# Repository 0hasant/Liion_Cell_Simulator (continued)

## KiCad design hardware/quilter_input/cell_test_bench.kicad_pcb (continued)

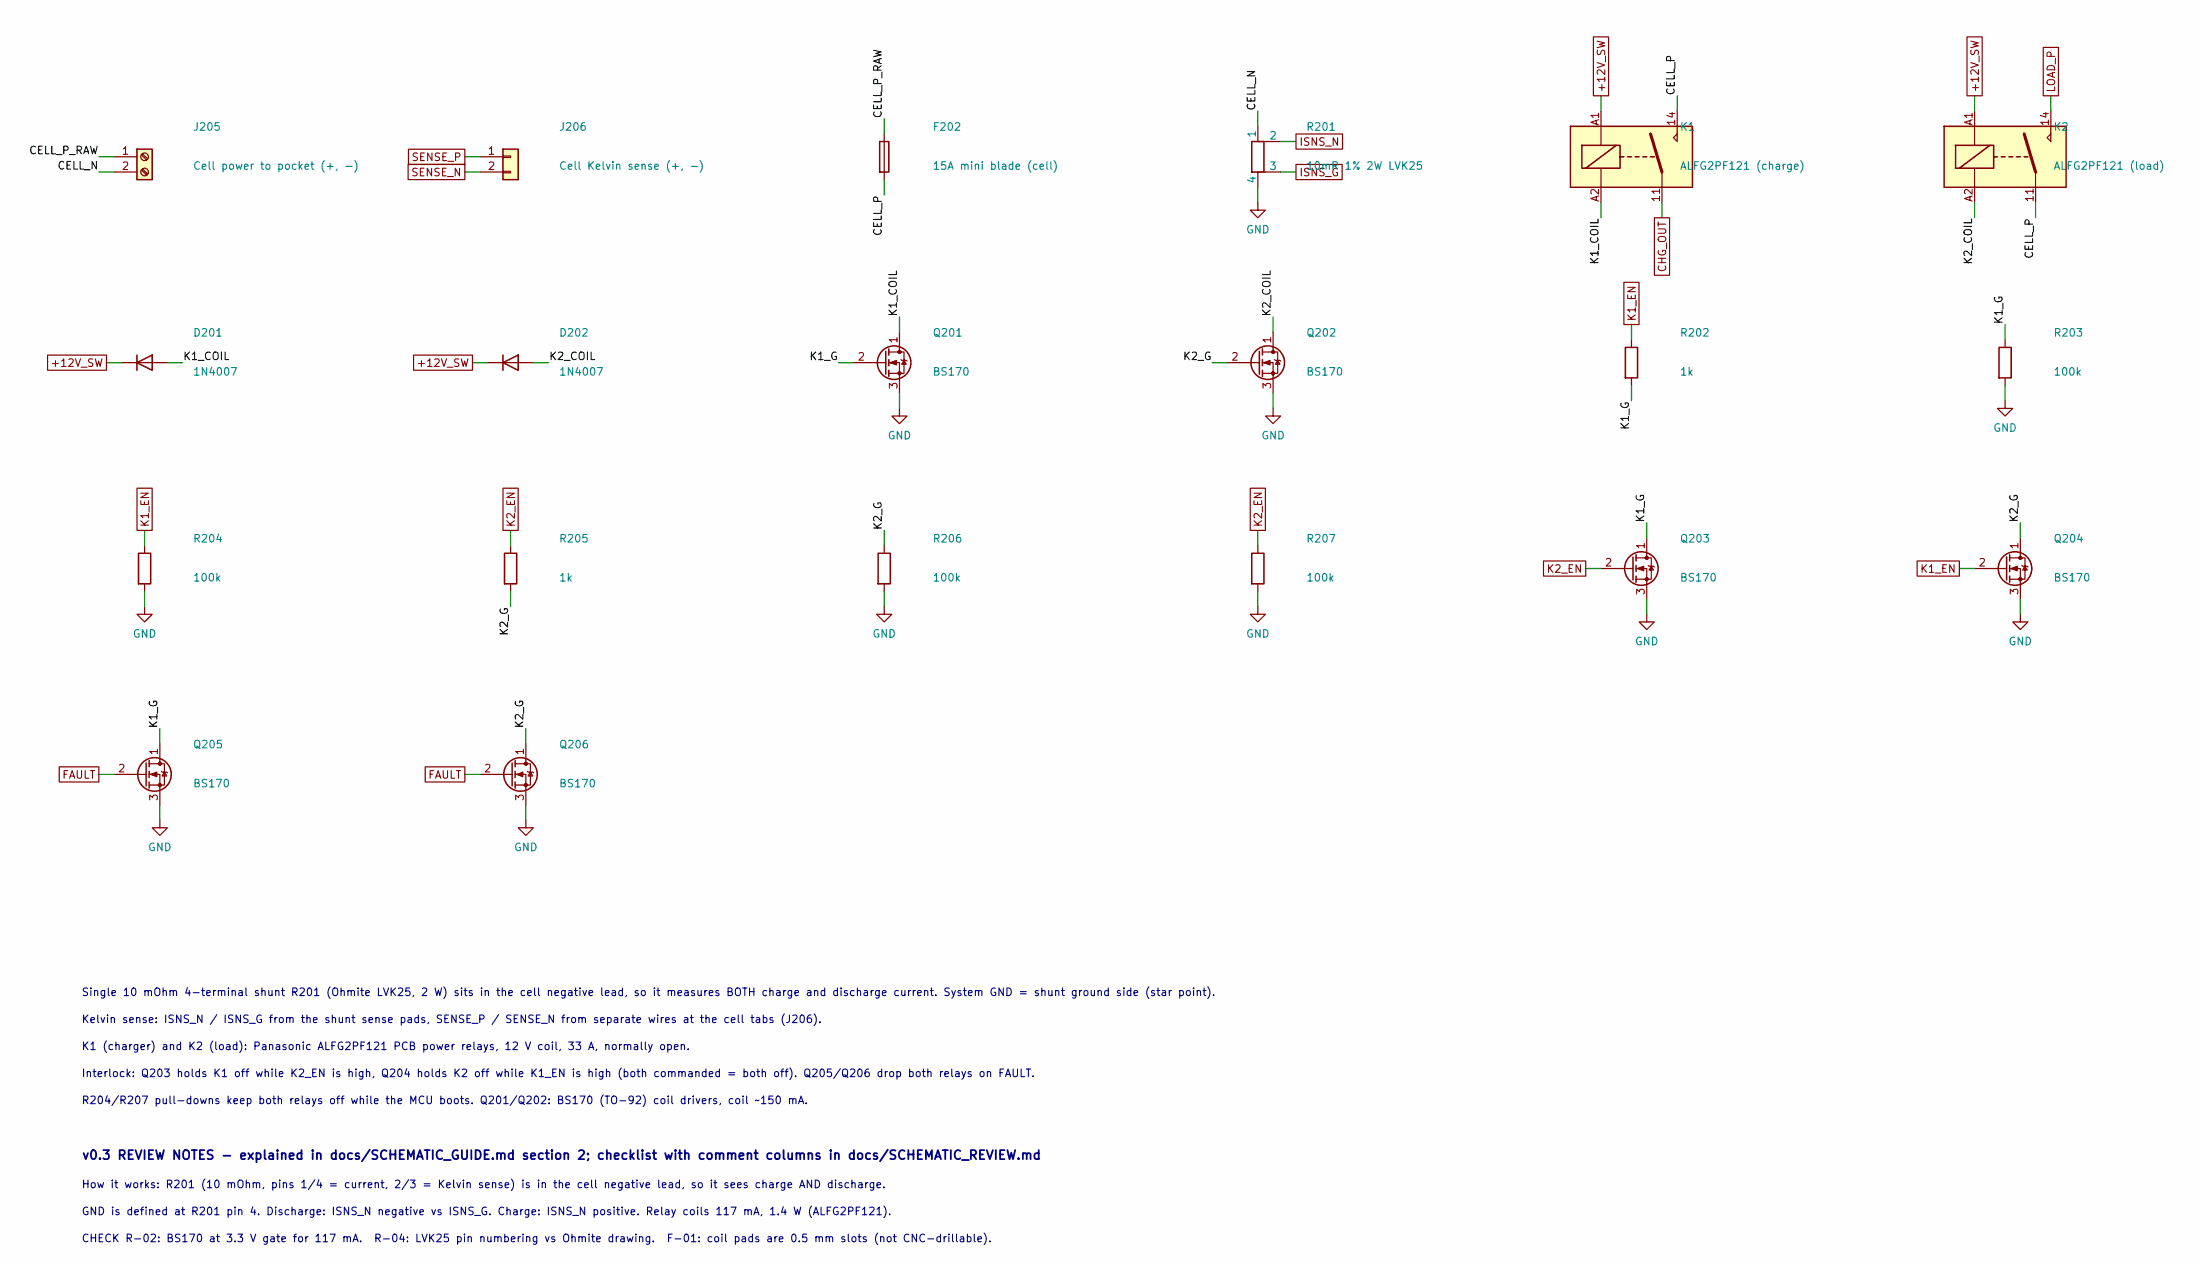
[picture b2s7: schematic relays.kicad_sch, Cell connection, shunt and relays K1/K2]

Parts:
D201, D202: 1N4007; D_DO-41_SOD81_P10.16mm_Horizontal; MPN 1N4007-E3/54
F202: 15A mini blade (cell); Fuseholder_Blade_Mini_Keystone_3568; MPN Keystone 3568
J205: Cell power to pocket (+, -); TerminalBlock_Phoenix_MKDS-3-2-5.08_1x02_P5.08mm_Horizontal
J206: Cell Kelvin sense (+, -); JST_XH_B2B-XH-A_1x02_P2.50mm_Vertical
K1: ALFG2PF121 (charge); Relay_SPST_Panasonic_ALFG_FormA; MPN ALFG2PF121
K2: ALFG2PF121 (load); Relay_SPST_Panasonic_ALFG_FormA; MPN ALFG2PF121
Q201, Q202, Q203, Q204, Q205, Q206: BS170; TO-92_Inline_Wide; MPN BS170
R201: 10mR 1% 2W LVK25; R_Shunt_Ohmite_LVK25; MPN LVK25R010FER
R202, R205: 1k; R_1206_3216Metric
R203, R204, R206, R207: 100k; R_1206_3216Metric

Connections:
+12V_SW: D201.1 (K), D202.1 (K), K1.A1, K2.A1; also elsewhere on the board
/Cell_Relays/CELL_N: J205.2, R201.1
/Cell_Relays/CELL_P: F202.2, K1.14, K2.11
/Cell_Relays/CELL_P_RAW: F202.1, J205.1
/Cell_Relays/K1_COIL: D201.2 (A), K1.A2, Q201.1 (D)
/Cell_Relays/K1_G: Q201.2 (G), Q203.1 (D), Q205.1 (D), R202.2, R203.1
/Cell_Relays/K2_COIL: D202.2 (A), K2.A2, Q202.1 (D)
/Cell_Relays/K2_G: Q202.2 (G), Q204.1 (D), Q206.1 (D), R205.2, R206.1
CHG_OUT: K1.11; also elsewhere on the board
FAULT: Q205.2 (G), Q206.2 (G); also elsewhere on the board
GND: Q201.3 (S), Q202.3 (S), Q203.3 (S), Q204.3 (S), Q205.3 (S), Q206.3 (S), R201.4, R203.2, R204.2, R206.2, R207.2; also elsewhere on the board
ISNS_G: R201.3; also elsewhere on the board
ISNS_N: R201.2; also elsewhere on the board
K1_EN: Q204.2 (G), R202.1, R204.1; also elsewhere on the board
K2_EN: Q203.2 (G), R205.1, R207.1; also elsewhere on the board
LOAD_P: K2.14; also elsewhere on the board
SENSE_N: J206.2; also elsewhere on the board
SENSE_P: J206.1; also elsewhere on the board

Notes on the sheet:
Single 10 mOhm 4-terminal shunt R201 (Ohmite LVK25, 2 W) sits in the cell negative lead, so it measures BOTH charge and discharge current. System GND = shunt ground side (star point).
Kelvin sense: ISNS_N / ISNS_G from the shunt sense pads, SENSE_P / SENSE_N from separate wires at the cell tabs (J206).
K1 (charger) and K2 (load): Panasonic ALFG2PF121 PCB power relays, 12 V coil, 33 A, normally open.
Interlock: Q203 holds K1 off while K2_EN is high, Q204 holds K2 off while K1_EN is high (both commanded = both off). Q205/Q206 drop both relays on FAULT.
R204/R207 pull-downs keep both relays off while the MCU boots. Q201/Q202: BS170 (TO-92) coil drivers, coil ~150 mA.
v0.3 REVIEW NOTES - explained in docs/SCHEMATIC_GUIDE.md section 2; checklist with comment columns in docs/SCHEMATIC_REVIEW.md
How it works: R201 (10 mOhm, pins 1/4 = current, 2/3 = Kelvin sense) is in the cell negative lead, so it sees charge AND discharge.
GND is defined at R201 pin 4. Discharge: ISNS_N negative vs ISNS_G. Charge: ISNS_N positive. Relay coils 117 mA, 1.4 W (ALFG2PF121).
CHECK R-02: BS170 at 3.3 V gate for 117 mA. R-04: LVK25 pin numbering vs Ohmite drawing. F-01: coil pads are 0.5 mm slots (not CNC-drillable).

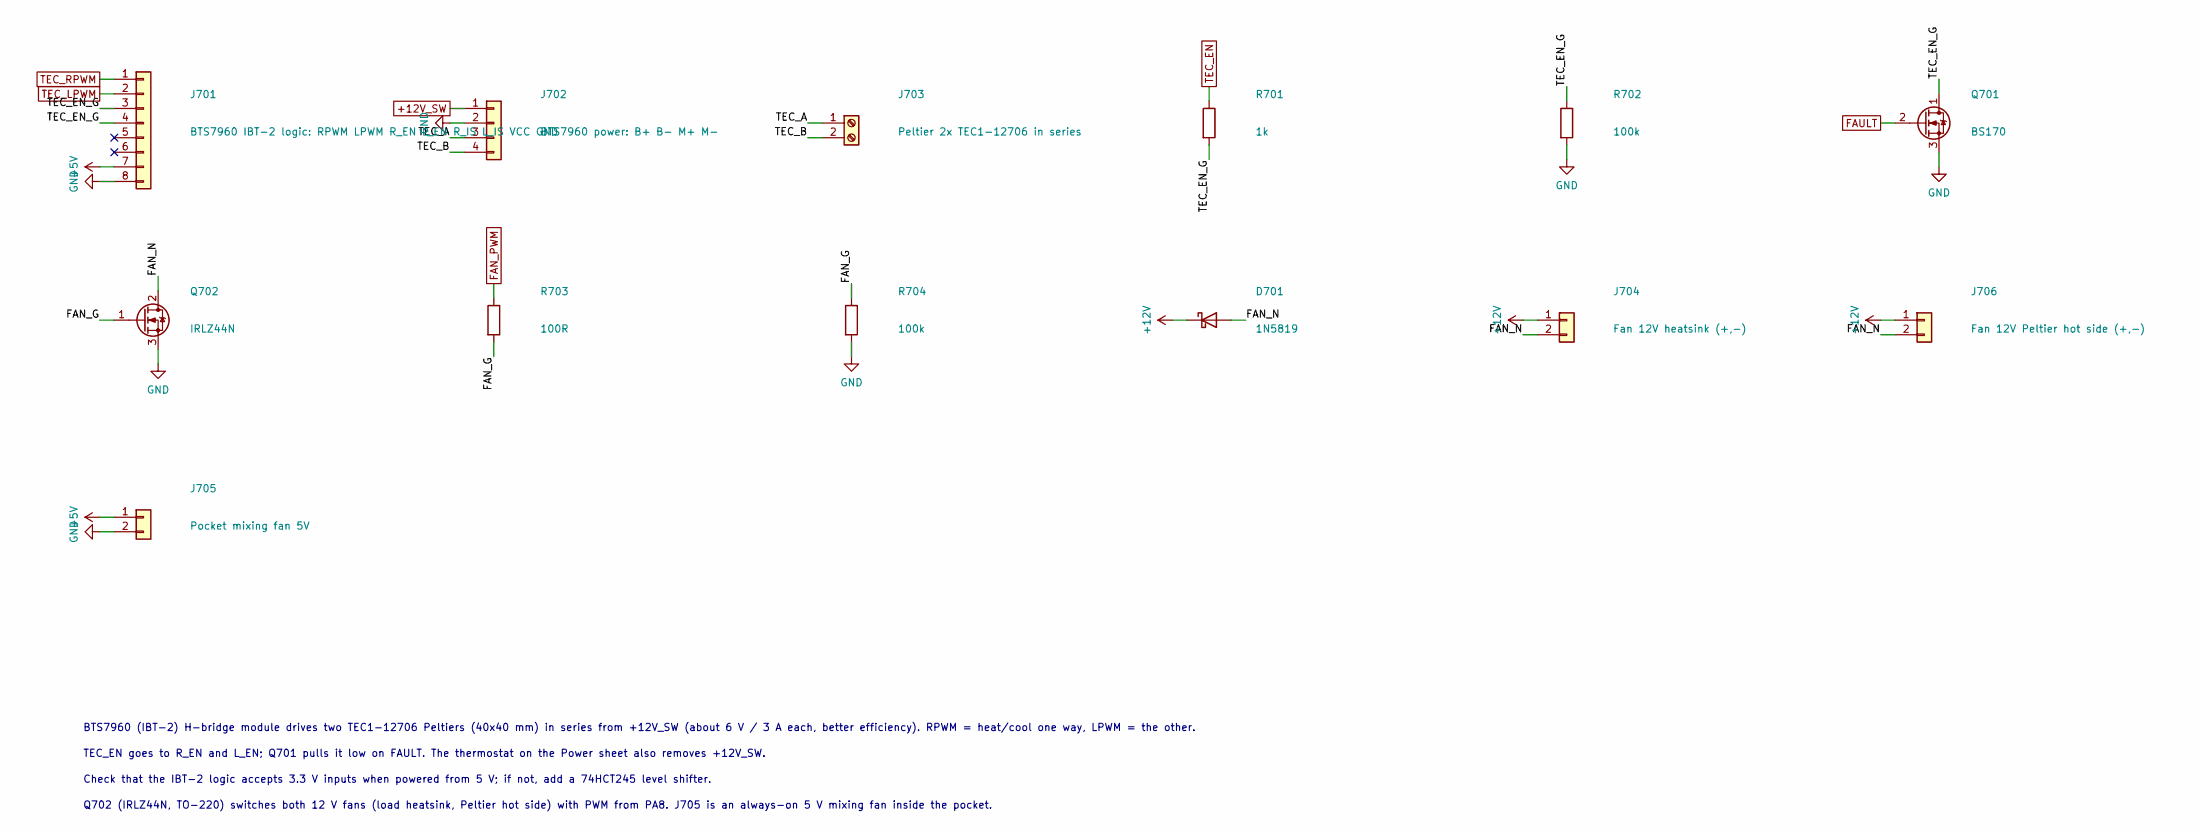
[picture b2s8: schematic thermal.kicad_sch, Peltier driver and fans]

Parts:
D701: 1N5819; D_DO-41_SOD81_P10.16mm_Horizontal; MPN 1N5819
J701: BTS7960 IBT-2 logic: RPWM LPWM R_EN L_EN R_IS L_I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; PinHeader_1x08_P2.54mm_Vertical
J702: BTS7960 power: B+ B- M+ M-; TerminalBlock_Phoenix_MKDS-1,5-4-5.08_1x04_P5.08mm_Horizont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
J703: Peltier 2x TEC1-12706 in series; TerminalBlock_Phoenix_MKDS-1,5-2-5.08_1x02_P5.08mm_Horizont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
J704: Fan 12V heatsink (+,-); JST_XH_B2B-XH-A_1x02_P2.50mm_Vertical
J705: Pocket mixing fan 5V; JST_XH_B2B-XH-A_1x02_P2.50mm_Vertical
J706: Fan 12V Peltier hot side (+,-); JST_XH_B2B-XH-A_1x02_P2.50mm_Vertical
Q701: BS170; TO-92_Inline_Wide; MPN BS170
Q702: IRLZ44N; TO-220-3_Vertical; MPN IRLZ44NPBF
R701: 1k; R_1206_3216Metric
R702, R704: 100k; R_1206_3216Metric
R703: 100R; R_1206_3216Metric

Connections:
+5V: J701.7, J705.1; also elsewhere on the board
+12V: D701.1 (K), J704.1, J706.1; also elsewhere on the board
+12V_SW: J702.1; also elsewhere on the board
/Thermal/FAN_G: Q702.1 (G), R703.2, R704.1
/Thermal/FAN_N: D701.2 (A), J704.2, J706.2, Q702.2 (D)
/Thermal/TEC_EN_G: J701.3, J701.4, Q701.1 (D), R701.2, R702.1
FAN_PWM: R703.1; also elsewhere on the board
FAULT: Q701.2 (G); also elsewhere on the board
GND: J701.8, J702.2, J705.2, Q701.3 (S), Q702.3 (S), R702.2, R704.2; also elsewhere on the board
unnamed: J702.3, J703.1
unnamed: J702.4, J703.2
TEC_EN: R701.1; also elsewhere on the board
TEC_LPWM: J701.2; also elsewhere on the board
TEC_RPWM: J701.1; also elsewhere on the board

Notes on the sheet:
BTS7960 (IBT-2) H-bridge module drives two TEC1-12706 Peltiers (40x40 mm) in series from +12V_SW (about 6 V / 3 A each, better efficiency). RPWM = heat/cool one way, LPWM = the other.
TEC_EN goes to R_EN and L_EN; Q701 pulls it low on FAULT. The thermostat on the Power sheet also removes +12V_SW.
Check that the IBT-2 logic accepts 3.3 V inputs when powered from 5 V; if not, add a 74HCT245 level shifter.
Q702 (IRLZ44N, TO-220) switches both 12 V fans (load heatsink, Peltier hot side) with PWM from PA8. J705 is an always-on 5 V mixing fan inside the pocket.

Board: 2 copper layers, 132 parts (0 on the bottom side), 68 nets, no tracks yet.

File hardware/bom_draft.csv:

Reference,Value,Sheet
J101,"PSU in 30V 10A (+, -)",Power
F101,10A,Power
D101,SMBJ33A (TVS),Power
C101,100uF 50V,Power
J102,12V buck module: IN+ IN- OUT+ OUT-,Power
C102,220uF 25V,Power
J103,5V buck module: IN+ IN- OUT+ OUT-,Power
C103,100uF 16V,Power
J104,Thermostat KSD9700 60C NC,Power
C104,220uF 25V,Power
J205,"Cell power to pocket (+, -)",Cell_Relays
J206,"Cell Kelvin sense (+, -)",Cell_Relays
F202,15A (cell),Cell_Relays
R201,10mR 4-terminal 1% 3W,Cell_Relays
K1,K1 charge relay socket: 85 86 30 87,Cell_Relays
K2,K2 load relay socket: 85 86 30 87,Cell_Relays
D201,1N4007,Cell_Relays
D202,1N4007,Cell_Relays
Q201,AO3400A,Cell_Relays
Q202,AO3400A,Cell_Relays
R202,1k,Cell_Relays
R203,100k,Cell_Relays
R204,100k,Cell_Relays
R205,1k,Cell_Relays
R206,100k,Cell_Relays
R207,100k,Cell_Relays
Q203,2N7002,Cell_Relays
Q204,2N7002,Cell_Relays
Q205,2N7002,Cell_Relays
Q206,2N7002,Cell_Relays
J301,Series R 0.1R 50W alu (off-board),Electronic_Load
Q301,IRFP260N,Electronic_Load
U302,"MCP4725 module #1 (A0=GND, 0x60): VCC GND SCL SDA A0 OUT",Electronic_Load
R301,29.4k 0.1%,Electronic_Load
R302,1k 0.1%,Electronic_Load
C301,10nF,Electronic_Load
R303,10k 0.1%,Electronic_Load
R304,10k 0.1%,Electronic_Load
Q302,2N7002,Electronic_Load
Q303,2N7002,Electronic_Load
R305,10k,Electronic_Load
U301,OPA2188,Electronic_Load
R306,10k,Electronic_Load
C302,1nF,Electronic_Load
R307,100R,Electronic_Load
R308,10k,Electronic_Load
R309,1k 0.1%,Electronic_Load
R310,12k 0.1%,Electronic_Load
R311,24.9k,Electronic_Load
R312,1k,Electronic_Load
R313,1k,Electronic_Load
D301,BAT54,Electronic_Load
D302,BAT54,Electronic_Load
C303,10nF,Electronic_Load
C304,100nF,Electronic_Load
C305,10uF,Electronic_Load
J401,XL4016 CC/CV module: IN+ IN- OUT+ OUT-,Charger
J402,"XL4016 FB tap (wire to FB pin, GND)",Charger
U401,"MCP4725 module #2 (A0=VCC, 0x61): VCC GND SCL SDA A0 OUT",Charger
R402,100R,Charger
C401,1uF,Charger
R401,1.2k,Charger
D401,BAT54,Charger
U501,ADS1115 module #1 (ADDR=GND): VDD GND SCL SDA ADDR ALRT A0 A1 A2 A3,Measurement
R501,100R,Measurement
R502,100R,Measurement
C501,100nF,Measurement
R503,10k 0.1%,Measurement
R504,10k 0.1%,Measurement
R505,100R,Measurement
C502,100nF,Measurement
U502,ADS1115 module #2 (ADDR=VDD): VDD GND SCL SDA ADDR ALRT A0 A1 A2 A3,Measurement
R506,10k 0.1%,Measurement
C503,100nF,Measurement
J501,NTC 10k cell,Measurement
R507,10k 0.1%,Measurement
C504,100nF,Measurement
J502,NTC 10k air,Measurement
R508,10k 0.1%,Measurement
C505,100nF,Measurement
J503,NTC 10k hs,Measurement
R509,10k 0.1%,Measurement
C506,100nF,Measurement
J504,NTC 10k tec,Measurement
R510,10k,Measurement
R511,10k,Measurement
C507,10nF,Measurement
R601,1k,Protection
U603,TL431,Protection
C601,100nF,Protection
R602,10k,Protection
R603,10k,Protection
R604,15k,Protection
R605,8.2k,Protection
R606,27k,Protection
R607,9.1k,Protection
R608,7.15k,Protection
R609,10k,Protection
U601,LM339,Protection
R610,5.6k,Protection
R611,10k,Protection
R612,20k,Protection
R613,100k,Protection
U602,LM393,Protection
C602,100nF,Protection
C603,100nF,Protection
R614,10k,Protection
Q601,2N7002,Protection
R615,10k,Protection
J701,BTS7960 IBT-2 logic: RPWM LPWM R_EN L_EN R_IS L_IS VCC GND,Thermal
J702,BTS7960 power: B+ B- M+ M-,Thermal
J703,Peltier x2 in series,Thermal
R701,1k,Thermal
R702,100k,Thermal
Q701,2N7002,Thermal
Q702,AO3400A,Thermal
R703,100R,Thermal
R704,100k,Thermal
D701,SS14,Thermal
J704,"Fans 12V: heatsink (+,-)",Thermal
J706,"Fans 12V: Peltier hot side (+,-)",Thermal
J705,Pocket mixing fan 5V,Thermal
J801,Blue Pill header A: B12 B13 B14 B15 A8 A9 A10 A11 A12 A15 B3 B4 B5 B6 B7 B8 B9 5V GND 3V3,MCU
J802,Blue Pill header B: VB C13 C14 C15 A0 A1 A2 A3 A4 A5 A6 A7 B0 B1 B10 B11 RST 3V3 GND GND,MCU
D801,SS14,MCU
J803,Debug UART: TX RX GND,MCU
R801,4.7k DNP,MCU
R802,4.7k DNP,MCU
C801,10uF,MCU

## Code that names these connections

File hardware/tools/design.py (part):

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
# ============================================================ ELECTRONIC LOAD
p = sheet('load', 'Electronic_Load', 'load.kicad_sch', 'Electronic load 0-10 A (linear, CC)', [
    'Setpoint: PWM from PA6 (TIM3_CH1), filtered by R1/C1 and R2/C2, divided by R3/R4: SETP = PWM x 3.3 V / 27.8 = 0-119 mV.',
    'CC loop: INP = (SETP - I x 10 mOhm)/2. U1A integrates (R7, C4) until INP equals INN, so I = (SETP - 2 x INN)/10 mOhm. R8 biases INN by +2.5 mV, so PWM = 0 always means zero current.',
    'Full scale about 11.3 A (firmware limits to 10 A). Q1 IRFP260N works in linear mode on the heatsink; the external 0.1 Ohm 50 W resistor (J1) shares the heat.',
    'Load off: LOAD_OFF is pulled up to +5 V (R10) and lifts INN to 0.4 V through D1/R9, so the op-amp output goes to 0 V. The MCU pulls PB14 low (open drain) to enable the load.',
    'Hardware fault: K4_COIL rises to 12 V when the safety switch drops, and lifts INN through D2/R11. K2 opens a few ms later.',
    'U1B: current monitor I_MON = 1.707 V + 0.12 V/A (discharge positive), for the MCU ADC (PA0), the OC comparators and the charger current limit.',
    'U1 = OPA2171 (SOIC-8, soldered on the copper side). R19/C6/C7 filter the op-amp supply +12VA (also feeds U401). How it works / what to check: docs/SCHEMATIC_GUIDE.md section 3.',
])
p += [
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    'Set the module CV pot to 4.25 V with no load BEFORE wiring the FB tap, and turn its CC pot fully up. 4.25 V is the hardware ceiling: both loops below can only LOWER the output.',
    'Voltage (CV): PWM from PA7, filtered by R1/C1, R2/C2, injects current into the XL4016 FB pin (1.25 V) through D1. PWM = 0 gives the ceiling; more PWM gives less voltage.',
    'Current (CC): U1A compares I_MON with ILIM and, when the charge current is above the limit, injects into FB through R5/D2. This is a hardware current limit (review item C-01).',
    'ILIM: PWM from PB0 through R6, with R7 to +3V3. PB0 high-Z (reset) = 3.3 V = zero current allowed. PWM 0 % = 5.6 A, 30 % = 0 A.',
    'U1B buffers SENSE_P (V_CELL), so the protection dividers and V_FAST do not load the cell (review item M-04). R9 makes "no cell" read 0 V.',
    'Firmware still matches the module voltage to the cell before closing K1, then raises voltage and current targets. How it works: docs/SCHEMATIC_GUIDE.md section 4.',
])
p += [
    hdr('J1', 'XL4016 CC/CV module: IN+ IN- OUT+ OUT-', ['VIN', 'PGND', 'CHG_OUT', 'PGND'], TB(4), 'TB4'),
    hdr('J2', 'XL4016 FB tap (pin 1 to the FB pin; pin 2 spare GND)', ['XL_FB', 'GND'], TB(2), 'TB2S'),
    res('R1', '560R', 'PWM_C', 'DC1'),
    cap('C1', '10uF 25V', 'DC1', 'GND'),
    res('R2', '560R', 'DC1', 'DAC_C'),
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p = sheet('meas', 'Measurement', 'measurement.kicad_sch', 'Measurement: ADS1115, NTCs, fast voltage', [
    'ADS1115 module (0x48): A0-A1 differential = shunt (current, +-256 mV range, 0.8 mA per bit), A2-A3 differential = cell voltage / 2 (Kelvin, +-2.048 V range).',
    'R3/R4 set the voltage accuracy. With 1 % parts, calibrate once against a DMM (two points) and store the gain in firmware.',
    'Four NTCs (10k, 10k pull-up to +3V3) go to the MCU ADC (PA2-PA5): cell surface, pocket air, load heatsink, Peltier hot side. NTC_HS and NTC_CELL also feed the OT comparators.',
    'V_FAST: buffered cell voltage / 2 for the MCU ADC (PA1), for the fast voltage step at a current edge (R0). It is ground-referenced: subtract I x 10 mOhm in firmware.',
    'How it works / what to check: docs/SCHEMATIC_GUIDE.md section 5.',
])
p += [
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p = sheet('prot', 'Protection', 'protection.kicad_sch', 'Hardware protection (independent of firmware), latched', [
    'VREF = 2.495 V from TL431 (U3). C1 must be 10 uF: a TL431 can oscillate with 10 nF - 3 uF on its output.',
    'Six trips pull FAULT_N low (open-collector, wired-OR): OV cell > 4.33 V | UV cell < 1.96 V | discharge > 11.6 A | charge > 6.2 A | heatsink or cell NTC > about 62 C.',
    'Latch (U2C): once FAULT_N has been low for about 1 ms it is held low. The MCU re-arms by driving ARM (PB10) high for a moment, and can force a trip by driving ARM low. Normally ARM is high-Z.',
    'Power-up state is "tripped": FAULT_N low, K4 off, +12V_SW dead, load off. Nothing moves until the firmware arms the bench. No USB (no +3V3) also means tripped.',
    'U2D turns FAULT_N into SW_B, which drives the safety switch K4 (Power sheet). UV also trips with no cell inserted.',
    'How it works / what to check: docs/SCHEMATIC_GUIDE.md section 6.',
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# ============================================================ THERMAL
p = sheet('thermal', 'Thermal', 'thermal.kicad_sch', 'Peltier driver and fans', [
    'Two TEC1-12706 Peltiers in series on J2 (about 6 V / 3 A each). Q3 (IRLZ44N, logic level) switches them with PWM from PB8 (TIM4_CH3).',
    'K3 swaps the polarity: relaxed = cool the pocket, energised (TEC_DIR, PB9) = heat. Firmware sets PWM to 0 before it toggles K3.',
    'Peltier and K3 run from +12V_SW, so any fault (or the thermostat) switches the Peltiers off. This replaces the BTS7960 module (cheaper, and no 3.3 V logic problem).',
    'Q2 (BC337) switches both 12 V heatsink fans with PWM from PA8. J5 is the always-on 12 V pocket mixing fan.',
    'How it works / what to check: docs/SCHEMATIC_GUIDE.md section 7.',
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p = sheet('mcu', 'MCU', 'mcu.kicad_sch', 'Blue Pill (STM32F103C8) and interfaces', [
    'Blue Pill plugs into two 1x20 female headers, 15.24 mm (0.6 in) apart. USB goes to the PC (USB CDC for the Python UI) and also powers the Blue Pill.',
    'JP1 is normally OPEN: the Blue Pill 5V pin is wired straight to USB VBUS, so the board must not feed it while a PC is connected (review item U-01). Close JP1 only to run without USB.',
    'ADC: PA0 I_MON, PA1 V_FAST, PA2-PA5 NTCs. PWM "DACs": PA6 load setpoint, PA7 charger voltage, PB0 charger current limit (TIM3). PA8 fans (TIM1). PB8 Peltier PWM (TIM4), PB9 Peltier direction.',
    'PB6/PB7 I2C1 (ADS1115 0x48). PB12 K1_EN, PB13 K2_EN. PB14 LOAD_OFF (open drain, 5 V pull-up, low = load on). PB15 FAULT_N (input). PB10 ARM (high-Z; pulse high = arm, low = trip).',
    'How it works / what to check: docs/SCHEMATIC_GUIDE.md section 8.',
])
p += [
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    hdr('J2', 'Blue Pill header B: VB C13 C14 C15 A0 A1 A2 A3 A4 A5 A6 A7 B0 B1 B10 B11 RST 3V3 GND GND',
        ['NC', 'NC', 'NC', 'NC', 'I_MON', 'V_FAST', 'NTC_CELL', 'NTC_AIR', 'NTC_HS', 'NTC_TEC', 'PWM_L', 'PWM_C',
         'PWM_I', 'NC', 'ARM', 'NC', 'NC', '+3V3', 'GND', 'GND'], SOCK(20), 'SOCK'),
    hdr('JP1', 'Board 5V to Blue Pill (normally open)', ['+5V', 'BP_J'], PINH(2), 'PINH'),
    diode('D1', SCHOTTKY, '1N5819', 'BP_5V', 'BP_J', FP_DO41),
    hdr('J3', 'Debug UART: TX RX GND', ['DBG_TX', 'DBG_RX', 'GND'], PINH(3), 'PINH'),
    cap('C1', '10uF 25V', '+3V3', 'GND'),
    flag('#FLG06', '+3V3'),
]
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                          lambda m: m.group(1) + str(PREFIX[k]) + '%02d' % int(m.group(2)), line)
            K.text(s, line, 25, ny + j * 4.5, 1.27)
    K.text(D.root, 'Cell test bench - schematic v%s. One 18650/21700 cell at a time; 0-10 A load, <=5 A charge, Peltier-controlled cell pocket.' % REV, 30, 30, 2)
    K.text(D.root, 'Inter-sheet connections use global labels. Power nets: GND (signal), PGND (power return), +12V, +5V, +3V3 (Blue Pill), VIN (30 V), +12V_SW (after safety switch K4).', 30, 38, 1.5)
    K.text(D.root, 'Single-sided board for in-house CNC milling. Explanation of every block: docs/SCHEMATIC_GUIDE.md.', 30, 44, 1.5)
    K.write_all(D, outdir)
    return D
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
